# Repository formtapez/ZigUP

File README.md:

# ZigUP
CC2530 based multi-purpose ZigBee Relais, Switch, Sensor and Router

[Bottom side](https://raw.githubusercontent.com/formtapez/ZigUP/master/Pictures/bottom.jpg)

# Features

* [Small enough to fit under a normal lightswitch](https://raw.githubusercontent.com/formtapez/ZigUP/master/Pictures/size.jpg) in an european flush-mounted box ("Unterputzdose" - That´s the UP in ZigUP)
* integrated optional ZigBee Router functionality (extends the range of all your other devices)
* Powerful bistable relais for up to 10 amps load
* 2 Inputs for switches/buttons:
	* Input "KEY" directly toggles the relais and outputs a ZigBee message
	* Input "DIG" only outputs a ZigBee message - So your coordinator can decide if the relais has to be toggled or not.
* Input for 16 digital temperature (DS18B20) and 1 humidity sensors (DHT22/AM2302) (Measurements will be reported via ZigBee)
* Input for S0-Bus impulses from power-, water- or gas-meters. Count-Value will be reported via ZigBee)
* Output for one normal LED or up to 10 WS2812B/Neopixel RGB-LEDs (controllable via ZigBee)
* Analog input to measure voltages of up to 32 Volt. (Voltage will be reported via ZigBee)
* Fully equipped debug-port to allow CC Debugger flashing and packet sniffing

# Connection diagrams

# Compilation

1. Get **Z-Stack Home 1.2.2a.44539** from http://www.ti.com/tool/Z-STACK-ARCHIVE
2. Get **IAR Embedded Workbench for 8051** from https://www.iar.com/iar-embedded-workbench (you can use the free trial version for one month)
3. Clone ZigUP source to **\Projects\zstack\HomeAutomation\ZigUP\\**
4. Start **\ZigUP\CC2530DB\ZigUP.eww** to load project in IAR
5. Choose between **Router** and **EndDevice** configuration
6. Edit **\Projects\zstack\Tools\CC2530DB\f8wConfig.cfg** to select the ZigBee channel your coordinator is using.
7. Compile

# Flashing with CC Debugger
1. Get **SmartRF Flash Programmer v1.12.8 (not v2.x!)** from https://www.ti.com/tool/flash-programmer
2. Connect CC Debugger to the Debug-Port of ZigUP with an 1:1 cable.
3. Select "Program CCxxxx..." and "System-on-Chip" tab
4. Load HEX-File and perform "Erase, program and verify" action

# Packet Sniffing using CC Debugger
As an alternative usage of this board, it can be used as a ZigBee packet-sniffer in combination with the CC Debugger.
1. Get **PACKET-SNIFFER v2.18.1 (not SNIFFER-2 v1.x!)** from https://www.ti.com/tool/PACKET-SNIFFER
2. Connect CC Debugger to the Debug-Port of ZigUP with an 1:1 cable.
3. Select protocol "IEEE 802.15.4/ZigBee" and click "Start"
4. Change radio channel and click "Start"
5. Re-flash ZigUP firmware when you are done, because it was replaced by a sniffer-firmware.

# Bill of Materials (BOM)

Qty | Value | Package | Parts | URL (exemplary supplier)
:--:|:----- |:------- |:------|:------------------------
5 | 100 | R0805 | R1, R3, R5, R9, R10 | https://uk.farnell.com/multicomp/mcwr08x1000ftl/res-100r-1-0-125w-0805-thick-film/dp/2447552
1 | 1k | R0805 | R8 | https://uk.farnell.com/multicomp/mcsr08x102-jtl/res-1k-5-0-125w-0805-ceramic/dp/2074338
3 | 10k | R0805 | R2, R4, R6 | https://uk.farnell.com/multicomp/mcwr08x1002ftl/res-10k-1-0-125w-0805-thick-film/dp/2447553
1 | 27k | R0805 | R7 | https://uk.farnell.com/multicomp/mcwr08x2702ftl/res-27k-1-0-125w-thick-film/dp/2447620
2 | 100n | C0805 | C4, C5 | https://uk.farnell.com/multicomp/mcu0805r104kct/cap-0-1-f-50v-10-x7r-0805/dp/9406387
3 | 10µ | C0805 | C1, C3, C6 | https://uk.farnell.com/murata/grm21br61e106ma73l/cap-10-f-25v-20-x5r-0805/dp/2611941
1 | 220µ/6V3/EEEFK0J221P | PANASONIC_D | C2 | https://uk.farnell.com/panasonic/eeefk0j221p/cap-220-f-6-3v-radial-smd/dp/1850086
8 | 4148 | 1206 | D1 - D8 | https://uk.farnell.com/taiwan-semiconductor/ts4148-rxg/diode-small-signal-75v-0-15a-1206/dp/2708388
2 | IRFML8244 | SOT23 | T1, T2 | https://uk.farnell.com/infineon/irfml8244trpbf/mosfet-n-ch-25v-5-7a-sot23/dp/1857298
1 | IRM-02-3.3 | IRM-02 | IC1 | https://uk.farnell.com/mean-well/irm-02-3-3/power-supply-ac-dc-3-3v-0-6a/dp/2815480
1 | CC2530 | E18-MS1-PCB | IC2 | https://www.aliexpress.com/item/-/32803052003.html
1 | DSP2A-L2-DC3V | DSP2A-L2 | K1 | https://uk.farnell.com/panasonic-electric-works/dsp2a-l2-dc3v/relay-dpst-no-250vac-30vdc-5a/dp/2095635
1 | MST 2.5A 250V | MST | F1 | https://uk.farnell.com/multicomp/mst-2-5a-250v/fuse-radial-slow-blow-2-5a/dp/1566104
1 | Phoenix 1792876 | PTS-3 | X1 | https://uk.farnell.com/phoenix-contact/1792876/terminal-block-wire-to-brd-3pos/dp/2072378
2 | TE 1-2834021-4 | MSC4 | X2, X3 | https://uk.farnell.com/te-connectivity/1-2834021-4/tb-wire-to-board-4pos-26-20awg/dp/2610379
1 | DEBUG | MA05-2 | X4 | https://uk.farnell.com/amphenol-icc-fci/67997-210hlf/connector-header-10pos-2row-2/dp/2886080
1 | PCB | FR4 | all | Use [Gerber files](https://github.com/formtapez/ZigUP/tree/master/Layout/Gerber) or contact me if you need a bare PCB

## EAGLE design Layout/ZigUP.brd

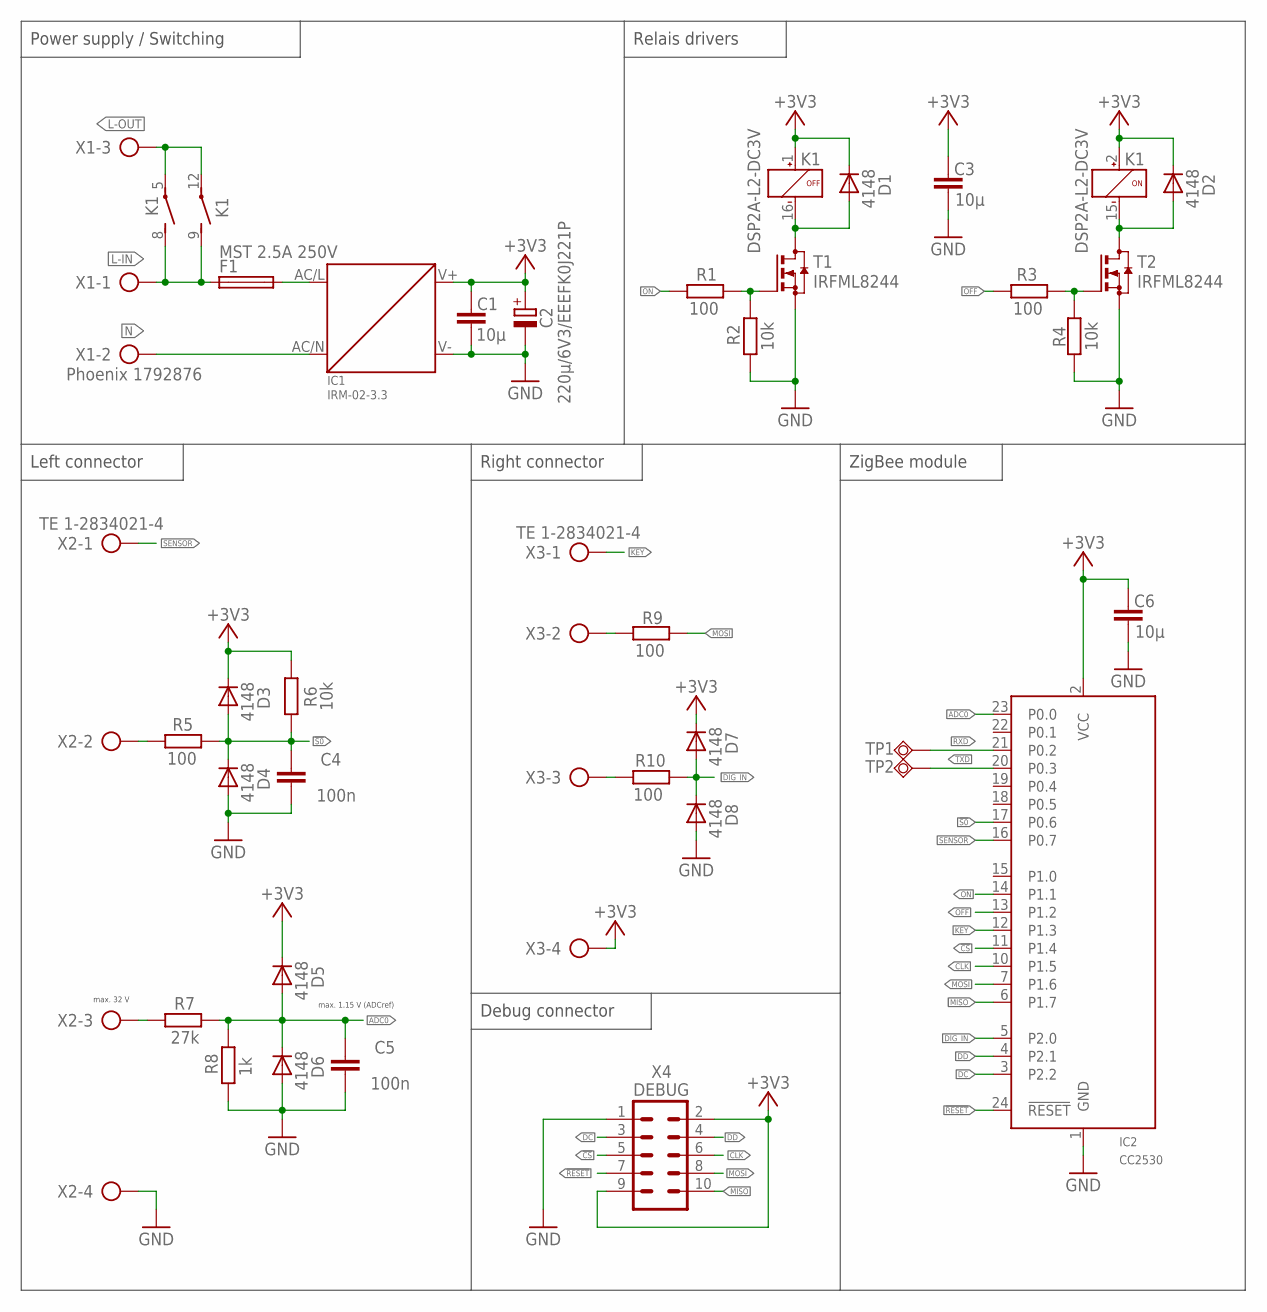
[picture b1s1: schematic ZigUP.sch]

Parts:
C1, C3, C6: 10µ; C0805
C2: 220µ/6V3/EEEFK0J221P; PANASONIC_D
C4, C5: 100n; C0805
D1, D2, D3, D4, D5, D6, D7, D8: 4148; 1206
F1: MST 2.5A 250V; MST
IC1: IRM-02-3.3; IRM-01
IC2: CC2530; E18-MS1-PCB
K1: DSP2A-L2-DC3V; DSP2A-L2
R1, R3, R5, R9, R10: 100; R0805
R2, R4, R6: 10k; R0805
R7: 27k; R0805
R8: 1k; R0805
T1, T2: IRFML8244; SOT23
TP1: RX; TP15SQ
TP2: TX; TP15SQ
X1: Phoenix 1792876; PTS-3
X2, X3: TE 1-2834021-4; MSC4
X4: DEBUG; MA05-2

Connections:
!CS: IC2.11 (P1.4), X4.5
!RESET: IC2.24 (!RESET), X4.7
!S0: C4.1, D3.A, D4.K, IC2.17 (P0.6), R5.2, R6.1
+3V3: C1.1, C2.+, C3.1, C6.1, D1.K, D2.K, D3.K, D5.K, D7.K, IC1.V+, IC2.2 (VCC), K1.1 (+), K1.2 (+), R6.2, X3.4, X4.2, X4.9
ADC0: C5.1, D5.A, D6.K, IC2.23 (P0.0), R7.2, R8.2
CLK: IC2.10 (P1.5), X4.6
DC: IC2.3 (P2.2), X4.3
DD: IC2.4 (P2.1), X4.4
DIG_IN: D7.A, D8.K, IC2.5 (P2.0), R10.2
GND: C1.2, C2.-, C3.2, C4.2, C5.2, C6.2, D4.A, D6.A, D8.A, IC1.V-, IC2.1 (GND), R2.1, R4.1, R8.1, T1.2 (S), T2.2 (S), X2.4, X4.1
KEY: IC2.12 (P1.3), X3.1
L-FUSED: F1.2, IC1.AC/L
L-IN: F1.1, K1.8 (C), K1.9 (C), X1.1
L-OUT: K1.5 (S), K1.12 (S), X1.3
MISO: IC2.6 (P1.7), X4.10
MOSI: IC2.7 (P1.6), R9.1, X4.8
N: IC1.AC/N, X1.2
unnamed: R7.1, X2.3
unnamed: D2.A, K1.15 (-), T2.3 (D)
unnamed: D1.A, K1.16 (-), T1.3 (D)
unnamed: R3.2, R4.2, T2.1 (G)
unnamed: R1.2, R2.2, T1.1 (G)
unnamed: R5.1, X2.2
unnamed: R9.2, X3.2
unnamed: R10.1, X3.3
OFF: IC2.13 (P1.2), R3.1
ON: IC2.14 (P1.1), R1.1
RXD: IC2.21 (P0.2), TP1.TP
SENSOR: IC2.16 (P0.7), X2.1
TXD: IC2.20 (P0.3), TP2.TP

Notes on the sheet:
max. 1.15 V (ADCref)
max. 32 V
Power supply / Switching
Relais drivers
Left connector
Right connector
Debug connector
ZigBee module

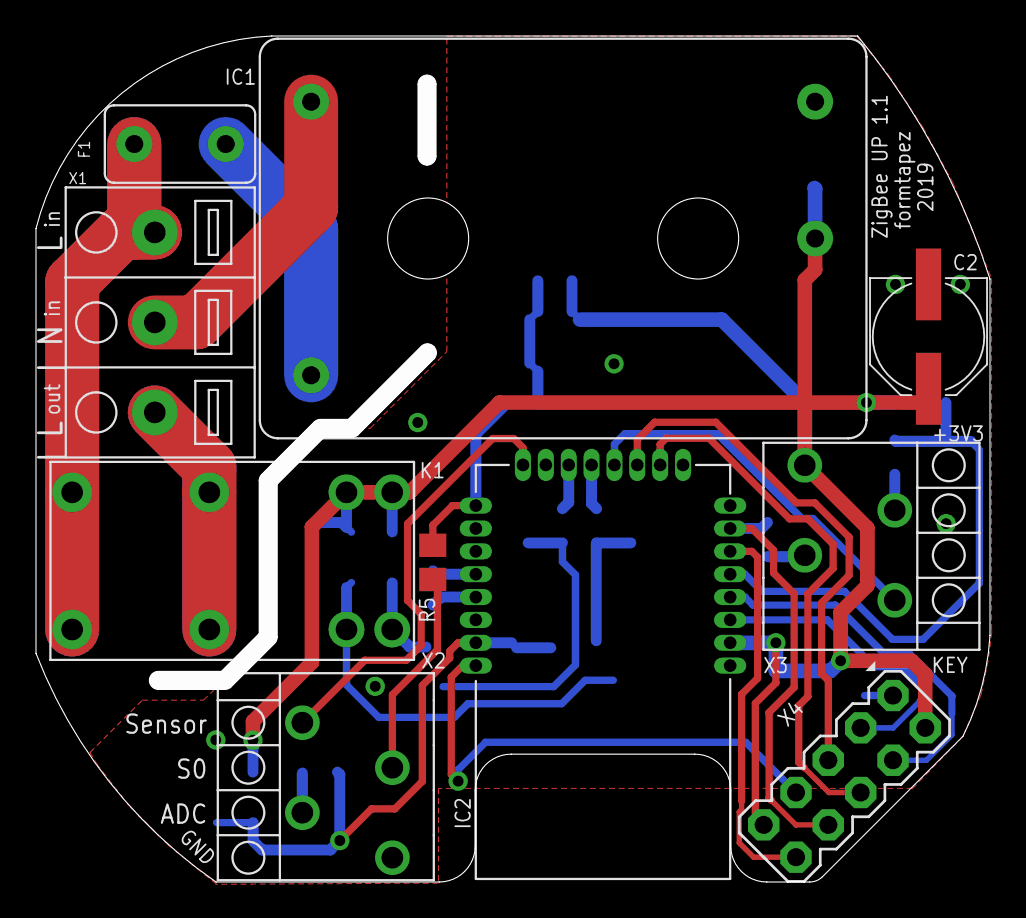
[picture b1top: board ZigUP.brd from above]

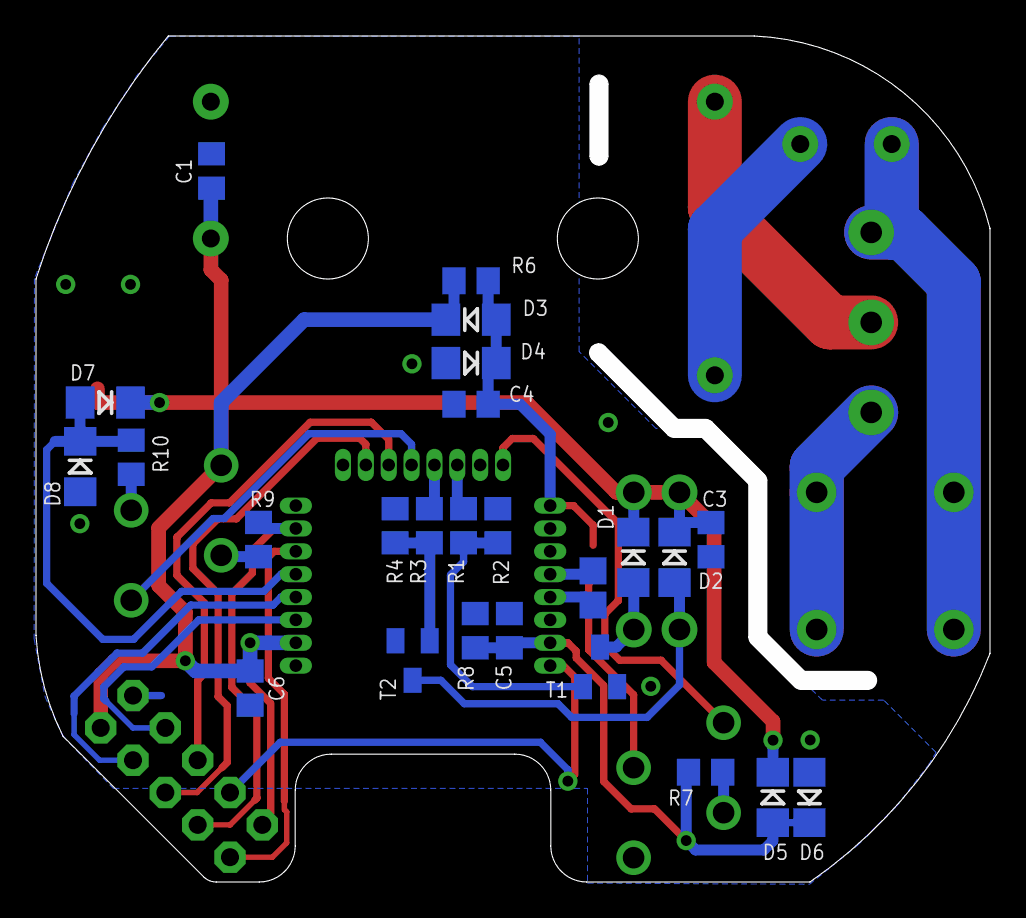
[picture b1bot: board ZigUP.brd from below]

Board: 2 copper layers, 53.0 x 47.0 mm, 36 parts (26 on the bottom side), 30 nets.

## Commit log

2019-04-30 added hardware related files
2019-04-30 added pictures
2019-04-30 added sourcecode
2019-04-30 readme test
2019-04-30 cleanup and function-splitup
2019-05-03 added connection drawings
2019-05-03 some documentation...
2019-05-03 implemented setcolor for ws2812b
2019-05-04 implemented LED control
2019-05-05 sensor autodetection
2019-05-10 added report-reason, removed non-router configurations, sensor checks
2019-05-18 Fixed LED-Control
2019-05-19 added BOM
2019-05-25 zigbee channel
2019-06-22 integrated EndDevice-only configuration
2019-08-21 Added support for 16 ds18b16 temperature sensors
2019-08-31 removed debouncing for S0-pulse to not loose it on nested interrupts
2019-09-01 fixed memory leak coused wrong initialization
2019-09-02 small fix of string length
2019-09-02 added temporarily unreleased converters for ds18b20 update
2019-09-02 fetched version from zigbee2mqtt-pullrequest
